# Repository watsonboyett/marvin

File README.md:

# Marvin

A chronically depressed and often bored robot that performs mundane tasks, despite being capable of great things...

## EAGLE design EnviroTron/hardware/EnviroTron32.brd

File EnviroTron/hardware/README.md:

# Revision History

## v2A

* Major redesign of hardware!
* Changed MCU to ESP32-WROOM
* Consolidated all parts to one PCB
* Changed mic circuit to use digital mic (no amplifier needed)

## v1A

* Initial design

## v1B

* Moved PIR output to D8 pin
* Fixed floating CSB pin on MS5607 chip 
* Added pull-down to PIR output

## v1C

* Changed pressure sensor to LPS22 chip
* Added microphone and amp
* Added 3v3 regulator (fed from 5v rail)
* Added current limiting resistor to PIR output

## v1D

* Added ADC chip for mic (ESP's ADC does not seem to meet noise specs when WiFi is used)
* Replaced 3v3 regulator with precision reference

## v1E

* Added Pi filter to create analog voltage rail
* Changed mic to SPH1642 part
* Increased mic amp gain

# Alternate Parts 

These are not intended to be drop-in replacements. These are parts that may provide similar performance and similar cost (or were found while performing initial component selection).

## MCU

* D1 Mini Pro - $5, 11 DIO, 1 AIO [web](https://www.wemos.cc/product/d1-mini-pro.html)

## Temp/Humidity

* SHT35 - $12, I2C, 0.1°C/1.5%RH accuracy
* SHT21 - $9, I2C, 0.5°C/2%RH accuracy
* SHT25 - $14, I2C, 0.2°C/1.8%RH accuracy
* Si7013 - $4, I2C, 0.4°C/3%RH accuracy

## Light

* APDS-9250 - $3, I2C, Separate R/G/B/Vis/IR channels
* LTR-329ALS-01 - $1, I2C, Separate Visible/IR channels
* TSL45315CL - $2, I2C, 
* PDV-P9203 - $2, Analog, 

## PIR

* EKMC1601112 - $12, Standard range/angle
* EKMC1603112 - $13, Long range, standard angle
* AMN34111 - $23, Wall range/angle

## Pressure

* LPS22HBTR - $4, I2C, high accuracy, decent range
* ICM-20789 - $9, I2C, 1hPa, 300hPa - 1100hPa (includes gyroscope and accelerometer)
* DPS422XTSA1 - $3, I2C, 0.06hPa/0.4°C, 300–1200 hPa

## Sound 

* (MIC) SPM0404HE5H-PB - $4
* (MIC) CMA-4544PF-W - $2
* (MIC) SPU0410HR5H-PB - $1
* (AMP) MCP6022T-I/ST - $2
* http://electronics.stackexchange.com/a/16596/83463
* http://electronics.stackexchange.com/a/58703/83463

## Air Quality

* AS-MLV-P2 - $25, CO/
* SGP30 - $14, MO Gas (CO2 Equivalent)
* CCS811B - $14, I2C, TVOC + eCO2

## Vibration/Acceleration

* D7S-A0001 - $30, 3 Axis

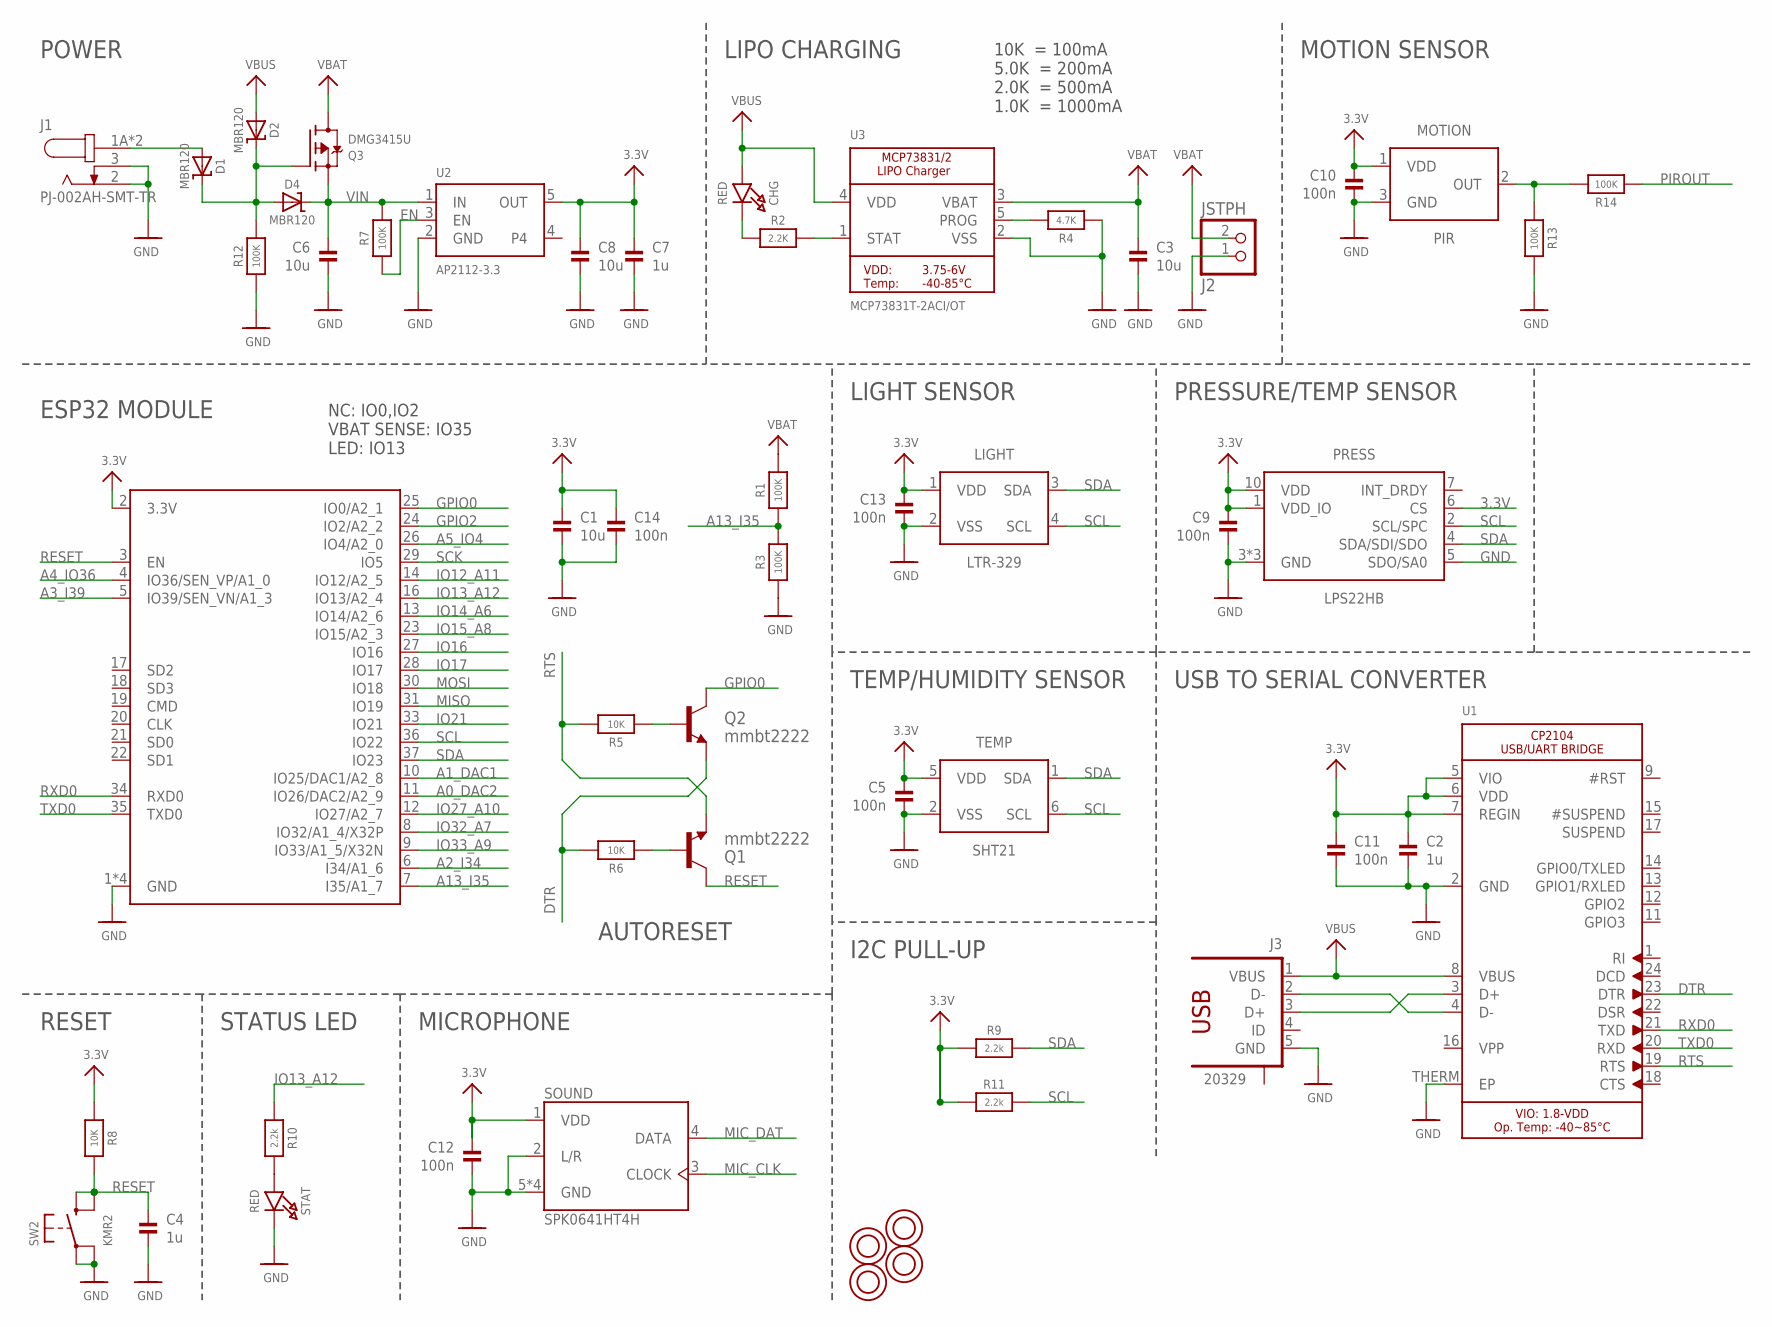
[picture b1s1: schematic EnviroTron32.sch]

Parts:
C1, C3, C6, C8: 10u; 0805-NO
C2: 1u; _0603
C4, C7: 1u; 0603-NO
C5, C9, C10, C11, C12, C13, C14: 100n; _0603
CHG: RED; CHIPLED_0805_NOOUTLINE
D1, D2, D4: MBR120; SOD-123
J1: PJ-002AH-SMT-TR; CUI_PJ-002AH-SMT-TR
J2: JSTPH; JSTPH2
J3: 20329; USB-10118192-0001LF
LIGHT: LTR-329; CHIPLED4
MOTION: PIR; CAN3
PRESS: LPS22HB; HLGA-10L
Q1, Q2: mmbt2222; SOT23-3
Q3: DMG3415U; SOT23-R
R1, R3, R7, R12, R13, R14: 100K; 0603-NO
R2: 2.2K; 0603-NO
R4: 4.7K; 0603-NO
R5, R6, R8: 10K; 0603-NO
R9, R10, R11: 2.2k; 0603-NO
SOUND: SPK0641HT4H; SPK0641HT4H-1
STAT: RED; CHIPLED_0805_NOOUTLINE
SW2: KMR2; BTN_KMR2_4.6X2.8
TEMP: SHT21; SHT2X-DFN6
U1: CP2104; QFN24_4MM_SMSC
U2: AP2112-3.3; SOT23-5
U3: MCP73831T-2ACI/OT; SOT23-5
U$17, U$31, U$32, U$34: TERM-7774
X2: ESP32_WROOM32_SKINNY; WROOM32_SKINNY

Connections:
3.3V: C1.1, C2.1, C5.1, C7.1, C8.1, C9.1, C10.1, C11.1, C12.1, C13.1, C14.1, LIGHT.1 (VDD), MOTION.1 (VDD), PRESS.1 (VDD_IO), PRESS.6 (CS), PRESS.10 (VDD), R8.1, R9.1, R11.1, SOUND.1 (VDD), TEMP.5 (VDD), U1.5 (VIO), U1.6 (VDD), U1.7 (REGIN), U2.5 (OUT), X2.2 (3.3V)
A0_DAC2: X2.11 (IO26/DAC2/A2_9)
A1_DAC1: X2.10 (IO25/DAC1/A2_8)
A2_I34: X2.6 (I34/A1_6)
A3_I39: X2.5 (IO39/SEN_VN/A1_3)
A4_IO36: X2.4 (IO36/SEN_VP/A1_0)
A5_IO4: X2.26 (IO4/A2_0)
A13_I35: R1.1, R3.2, X2.7 (I35/A1_7)
DCIN: D1.A, J1.1A (1), J1.1B (1)
DTR: Q2.2 (E), R6.2, U1.23 (DTR)
EN: R7.1, U2.3 (EN)
GND: C1.2, C2.2, C3.2, C4.2, C5.2, C6.2, C7.2, C8.2, C9.2, C10.2, C11.2, C12.2, C13.2, C14.2, J1.2, J1.3, J2.1, J3.5 (GND), LIGHT.2 (VSS), MOTION.3 (GND), PRESS.3 (GND), PRESS.5 (SDO/SA0), PRESS.8 (GND), PRESS.9 (GND), R3.1, R4.1, R12.1, R13.2, SOUND.2 (L/R), SOUND.5 (GND), SOUND.6 (GND), SOUND.7 (GND), SOUND.8 (GND), STAT.C, SW2.A, SW2.A' (P1), TEMP.2 (VSS), U1.2 (GND), U1.THERM (EP), U2.2 (GND), U3.2 (VSS), X2.1 (GND), X2.15 (GND), X2.38 (GND), X2.P$1 (GND)
GPIO0: Q2.3 (C), X2.25 (IO0/A2_1)
GPIO2: X2.24 (IO2/A2_2)
IO12_A11: X2.14 (IO12/A2_5)
IO13_A12: R10.1, X2.16 (IO13/A2_4)
IO14_A6: X2.13 (IO14/A2_6)
IO15_A8: X2.23 (IO15/A2_3)
IO16: X2.27 (IO16)
IO17: X2.28 (IO17)
IO21: X2.33 (IO21)
IO27_A10: X2.12 (IO27/A2_7)
IO32_A7: X2.8 (IO32/A1_4/X32P)
IO33_A9: X2.9 (IO33/A1_5/X32N)
MIC_CLK: SOUND.3 (CLOCK)
MIC_DAT: SOUND.4 (DATA)
MISO: X2.31 (IO19)
MOSI: X2.30 (IO18)
unnamed: CHG.C, R2.1
unnamed: J3.3 (D+), U1.3 (D+)
unnamed: R2.2, U3.1 (STAT)
unnamed: R4.2, U3.5 (PROG)
unnamed: R10.2, STAT.A
unnamed: J3.2 (D-), U1.4 (D-)
unnamed: D1.C, D2.C, D4.A, Q3.1 (G), R12.2
unnamed: MOTION.2 (OUT), R13.1, R14.2
unnamed: Q1.1 (B), R6.1
unnamed: Q2.1 (B), R5.1
PIROUT: R14.1
RESET: C4.1, Q1.3 (C), R8.2, SW2.B (S), SW2.B' (S1), X2.3 (EN)
RTS: Q1.2 (E), R5.2, U1.19 (RTS)
RXD0: U1.21 (TXD), X2.34 (RXD0)
SCK: X2.29 (IO5)
SCL: LIGHT.4 (SCL), PRESS.2 (SCL/SPC), R11.2, TEMP.6 (SCL), X2.36 (IO22)
SDA: LIGHT.3 (SDA), PRESS.4 (SDA/SDI/SDO), R9.2, TEMP.1 (SDA), X2.37 (IO23)
TXD0: U1.20 (RXD), X2.35 (TXD0)
VBAT: C3.1, J2.2, Q3.3 (D), R1.2, U3.3 (VBAT)
VBUS: CHG.A, D2.A, J3.1 (VBUS), U1.8 (VBUS), U3.4 (VDD)
VIN: C6.1, D4.C, Q3.2 (S), R7.2, U2.1 (IN)

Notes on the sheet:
POWER
RESET
10K = 100mA 5.0K = 200mA 2.0K = 500mA 1.0K = 1000mA
USB TO SERIAL CONVERTER
LIPO CHARGING
STATUS LED
ESP32 MODULE
NC: IO0,IO2 VBAT SENSE: IO35 LED: IO13
PRESSURE/TEMP SENSOR
MOTION SENSOR
LIGHT SENSOR
TEMP/HUMIDITY SENSOR
I2C PULL-UP
MICROPHONE
AUTORESET

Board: 4 copper layers, 57 parts (0 on the bottom side), 27 nets, no tracks yet.

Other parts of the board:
U$35, U$43, U$44, U$45: HOLE_4-40

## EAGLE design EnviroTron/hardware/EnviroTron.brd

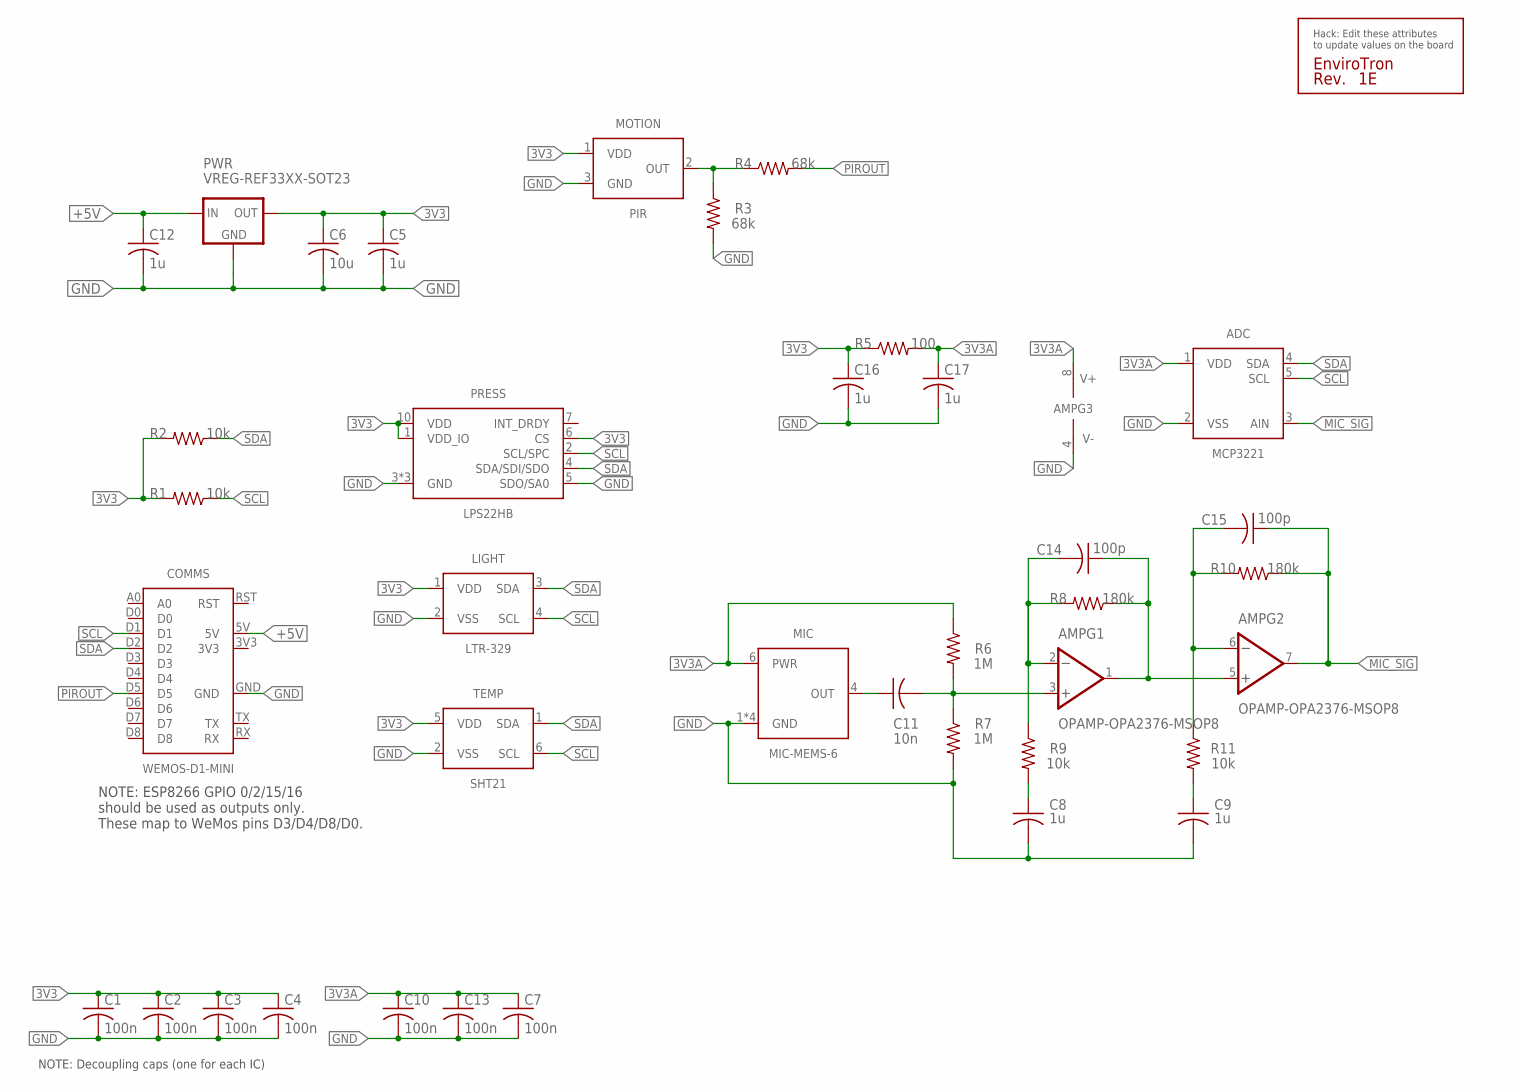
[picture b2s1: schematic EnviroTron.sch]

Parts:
ADC: MCP3221; SOT23-5
AMP: OPAMP-OPA2376-MSOP8; MSOP-8
C1, C2, C3, C4, C7, C10, C13: 100n; C0603
C5, C8, C9, C12, C16, C17: 1u; C0603
C6: 10u; C0805
C11: 10n; C0603
C14, C15: 100p; C0603
COMMS: WEMOS-D1-MINI
LIGHT: LTR-329; CHIPLED4
MIC: MIC-MEMS-6; DFN-6
MOTION: PIR; CAN3
PRESS: LPS22HB; HLGA-10L
PWR: VREG-REF33XX-SOT23; SOT23-3
R1, R2, R9, R11: 10k; R0603
R3, R4: 68k; R0603
R5: 100; R0603
R6, R7: 1M; R0603
R8, R10: 180k; R0603
TEMP: SHT21; SHT2X-DFN6
U$1: SILK_QC

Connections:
3V3: C1.1, C2.1, C3.1, C4.1, C5.1, C6.1, C16.1, LIGHT.1 (VDD), MOTION.1 (VDD), PRESS.1 (VDD_IO), PRESS.6 (CS), PRESS.10 (VDD), PWR.2 (OUT), R1.2, R2.2, R5.1, TEMP.5 (VDD)
3V3A: ADC.1 (VDD), AMP.8 (V+), C7.1, C10.1, C13.1, C17.1, MIC.6 (PWR), R5.2, R6.1
+5V: C12.1, COMMS.5V, PWR.1 (IN)
GND: ADC.2 (VSS), AMP.4 (V-), C1.2, C2.2, C3.2, C4.2, C5.2, C6.2, C7.2, C8.2, C9.2, C10.2, C12.2, C13.2, C16.2, C17.2, COMMS.GND, LIGHT.2 (VSS), MIC.1 (GND), MIC.2 (GND), MIC.3 (GND), MIC.5 (GND), MOTION.3 (GND), PRESS.3 (GND), PRESS.5 (SDO/SA0), PRESS.8 (GND), PRESS.9 (GND), PWR.3 (GND), R3.2, R7.2, TEMP.2 (VSS)
MIC_OUT: AMP.3 (+IN), C11.2, R6.2, R7.1
MIC_SIG: ADC.3 (AIN), AMP.7 (OUT), C15.1, R10.1
unnamed: AMP.1 (OUT), AMP.5 (+IN), C14.1, R8.1
unnamed: MOTION.2 (OUT), R3.1, R4.1
unnamed: AMP.2 (-IN), C14.2, R8.2, R9.1
unnamed: C8.1, R9.2
unnamed: C11.1, MIC.4 (OUT)
unnamed: AMP.6 (-IN), C15.2, R10.2, R11.1
unnamed: C9.1, R11.2
PIROUT: COMMS.D5, R4.2
SCL: ADC.5 (SCL), COMMS.D1, LIGHT.4 (SCL), PRESS.2 (SCL/SPC), R1.1, TEMP.6 (SCL)
SDA: ADC.4 (SDA), COMMS.D2, LIGHT.3 (SDA), PRESS.4 (SDA/SDI/SDO), R2.1, TEMP.1 (SDA)

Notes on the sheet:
NOTE: Decoupling caps (one for each IC)
NOTE: ESP8266 GPIO 0/2/15/16 should be used as outputs only. These map to WeMos pins D3/D4/D8/D0.

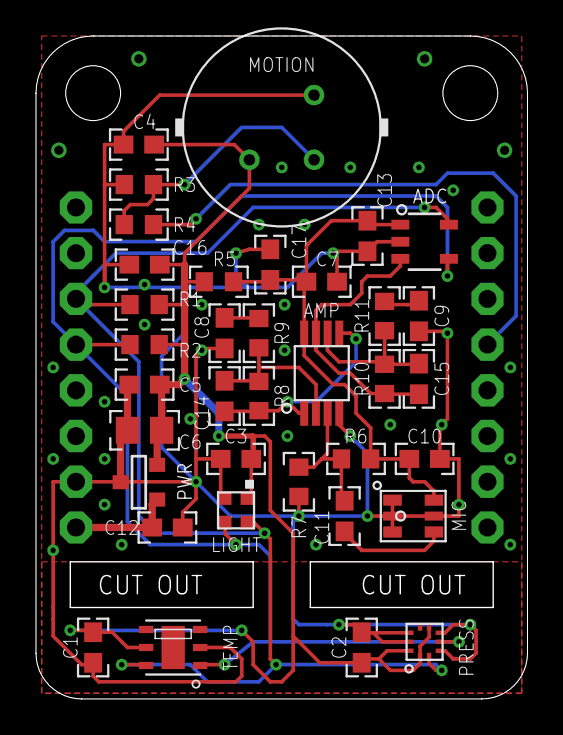
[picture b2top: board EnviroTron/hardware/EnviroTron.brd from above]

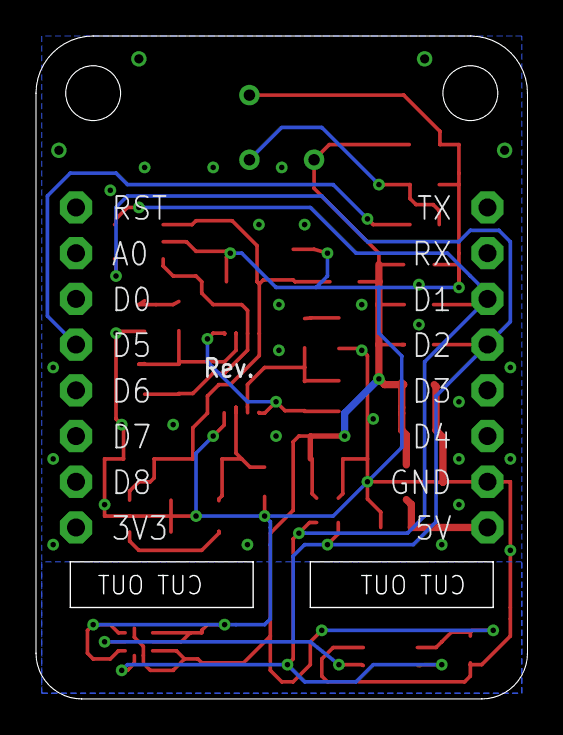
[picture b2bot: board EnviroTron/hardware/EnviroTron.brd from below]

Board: 2 copper layers, 27.2 x 36.8 mm, 38 parts (2 on the bottom side), 16 nets.

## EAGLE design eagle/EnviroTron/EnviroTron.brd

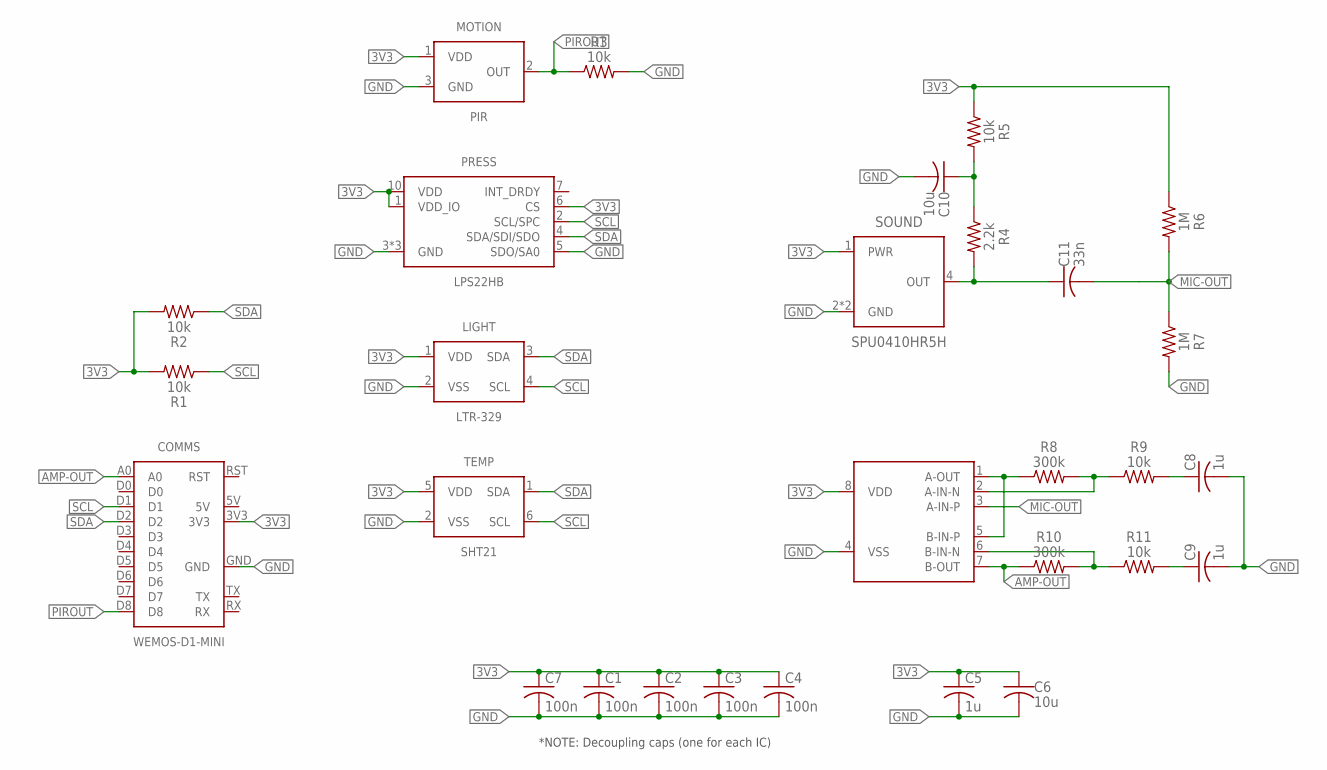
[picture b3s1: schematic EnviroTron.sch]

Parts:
C1, C2, C3, C4, C7: 100n; C0603
C5, C8, C9: 1u; C0603
C6, C10: 10u; C0805
C11: 33n; C0805
COMMS: WEMOS-D1-MINI
LIGHT: LTR-329; CHIPLED4
MOTION: PIR; CAN3
PRESS: LPS22HB; HLGA-10L
R1, R2, R3, R5, R9, R11: 10k; R0603
R4: 2.2k; R0603
R6, R7: 1M; R0603
R8, R10: 300k; R0603
SOUND: SPU0410HR5H; BPAD-4
TEMP: SHT21; SHT2X-DFN6
U$1: MCP6002; MSOP-8

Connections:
3V3: C1.1, C2.1, C3.1, C4.1, C5.1, C6.1, C7.1, COMMS.3V3, LIGHT.1 (VDD), MOTION.1 (VDD), PRESS.1 (VDD_IO), PRESS.6 (CS), PRESS.10 (VDD), R1.2, R2.2, R5.1, R6.1, SOUND.1 (PWR), TEMP.5 (VDD), U$1.8 (VDD)
AMP-OUT: COMMS.A0, R10.1, U$1.7 (B-OUT)
GND: C1.2, C2.2, C3.2, C4.2, C5.2, C6.2, C7.2, C8.2, C9.2, C10.2, COMMS.GND, LIGHT.2 (VSS), MOTION.3 (GND), PRESS.3 (GND), PRESS.5 (SDO/SA0), PRESS.8 (GND), PRESS.9 (GND), R3.2, R7.2, SOUND.2 (GND), SOUND.3 (GND), TEMP.2 (VSS), U$1.4 (VSS)
MIC-OUT: C11.2, R6.2, R7.1, U$1.3 (A-IN-P)
unnamed: R8.1, U$1.1 (A-OUT), U$1.5 (B-IN-P)
unnamed: C10.1, R4.1, R5.2
unnamed: R8.2, R9.1, U$1.2 (A-IN-N)
unnamed: C8.1, R9.2
unnamed: C11.1, R4.2, SOUND.4 (OUT)
unnamed: R10.2, R11.1, U$1.6 (B-IN-N)
unnamed: C9.1, R11.2
PIROUT: COMMS.D8, MOTION.2 (OUT), R3.1
SCL: COMMS.D1, LIGHT.4 (SCL), PRESS.2 (SCL/SPC), R1.1, TEMP.6 (SCL)
SDA: COMMS.D2, LIGHT.3 (SDA), PRESS.4 (SDA/SDI/SDO), R2.1, TEMP.1 (SDA)

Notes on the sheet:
*NOTE: Decoupling caps (one for each IC)

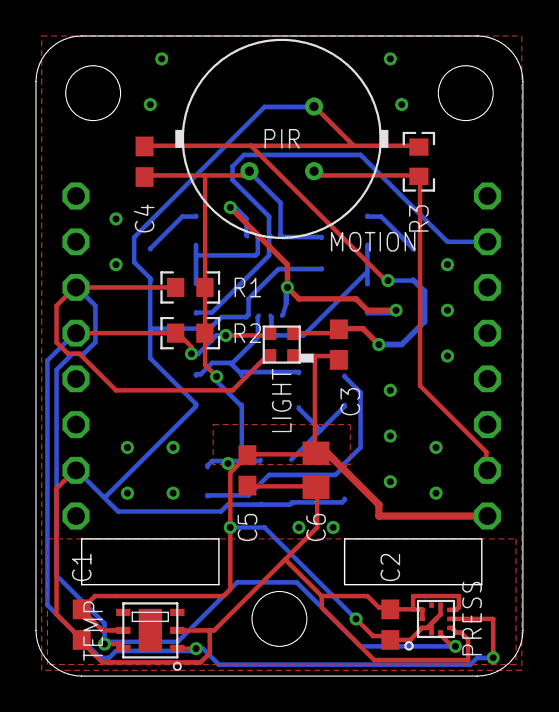
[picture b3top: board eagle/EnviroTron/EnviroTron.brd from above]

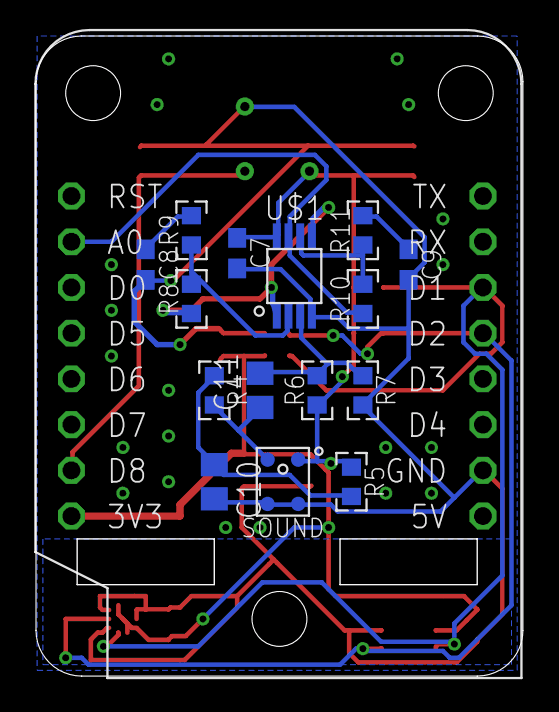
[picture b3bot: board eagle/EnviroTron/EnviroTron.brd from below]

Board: 2 copper layers, 27.0 x 35.5 mm, 29 parts (16 on the bottom side), 14 nets.

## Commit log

2016-01-13 Initial commit.
2016-01-14 Update README.md
    Added slightly more to the description.
2016-06-19 Added header info about how to "install" the python script
2016-06-19 Added info about how to load custom web apps
2016-06-19 Added setup and installation info
2016-06-19 Edited formatting of main readme
2016-06-19 Formatting changes for main readme file
2016-08-12 Added script to collect internet speed (DL/UL) data
2016-11-06 Added Arduino/Wemos Temperature and Thermostat projects
2016-11-06 Added information about initial setup and configuration of server
2016-12-31 Created EnviroTron schematic and board
2017-01-02 converted influx URL params to macros
2017-01-10 Cleaned up small layout details
2017-01-23 Created Arduino project for Envirotron boards
2017-01-24 Added register definitions for SHT21 and MS5607 chips
2017-01-24 Fixed floating CSB pin on MS5607 chip
2017-01-25 Implemented SHT21 sensor reading logic and moved PIR input to D8 pin.
2017-03-28 Added LPS22HB part to library.
2017-04-07 Added sound sensor to EnviroTron board. Swapped to better Pressure sensor.
2017-04-07 Added DC blocking cap to mic pre-amp circuit.
2017-04-09 Completed initial routing of all signals for new board layout.
2017-05-03 Reorganized files into project based structures
2017-05-24 Added support for MS5607. Improved support for other sensors.
2017-05-24 Added support for LPS22HB pressure sensor chip.
2017-05-27 Refactored sensor logic into their own files. All sensors seem to be working as they should now.
2017-05-27 Starting to update ThermoBot to use EnviroTron sensor nodes.
2017-05-29 Added support for writing sensor data to influx db
2017-06-11 Added MUX to allow for hardware defined device IDs. Moved PIR input to pin that doesn't affect bootloader operation.
2017-06-11 Consolidated all parts to EnviroTron library. Cleaned up schematic and layout.
2017-06-11 Updated firmware to move PIR input to D5 pin.
2017-07-16 Improved mic function interface. Improved calibration offsets for temperature sensors.
2017-07-17 Redesigned board so that all components are on one side. Fixed some issues discovered through testing.
2017-07-18 Trying to fix spurious reboot issue.
2017-07-20 Attempting to fix ADC noise by preventing ESP from sleeping.
2017-08-08 Added 3v3 regulator; finalized layout and BOM
2017-08-09 Fixed silkscreen name and value placements. Created MFG and archive files for v1C.
2017-08-25 Added ADC in place of noisy ESP8266 ADC. Switched to precision reference for voltage source.
2017-12-10 Renamed ThermoBot to ThermoTron and reorganized firmware files
2017-12-10 Changed PIR input pin.
2017-12-10 Reorganized some files. Added some python scrapers and collection scripts.
2017-12-11 Added support for MSP3221 ADC for MIC sensor. Added common function/macros file and cleaned up existing usages.
2017-12-12 Fixed some bugs related to the mic input
2017-12-21 Refactored mic and ADC logic into separate modules.
2017-12-21 Added initial support for mqtt publishing
2017-12-21 Moved MQTT and Wifi code into seprate module
2018-01-07 Changed mic to new part. Added Pi filter for analog voltage rail.
2018-01-09 Added PI filter to create analog voltage rail. Increased mic amp gain. Replaced mic with lower noise device.
2019-10-09 Checking in current state before starting totally new hardware version
2019-10-10 Started V2 of EnviroTron

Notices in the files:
EnviroTron/hardware/EnviroTron.sch:
CONTACT_ADDRESS: Licensed under CC-BY-SA
CONTACT_PHONE: (Creative Commons, Attribution + Share Alike)
